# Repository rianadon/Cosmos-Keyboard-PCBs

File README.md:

# Cosmos Keyboard PCBs

This repository contains the sources and specs for the PCBs I've made for my pet project, [Cosmos Keyboard Generator](https://ryanis.cool/cosmos).

## Plum Twist

A single-key PCB, with hotswap and RGB support that locks into place. [[Main Website](https://ryanis.cool/cosmos/plum-twist/)] [[Buy](https://cosmos-store.ryanis.cool/products/plum-twist)]

It's similar in functionality to the [Amoeba PCBs](https://github.com/JKing-B16/keyboard-pcbs) (in fact I've used some of the same footprints), but I've switched to large SMD pads to make wiring easier and designed the footprint to twist into a custom socket.

The version here on GitHub is pared down in terms of artwork and panelization, as my goal here is to make it easy for you to produce your own functionally identical version, not copy 1:1 what I sell. It's cheaper through JLC to buy the non-panelized version anyways. See the [subfolder's README](./plum-twist/README.md) for instructions on manufacturing these yourself.

Pinouts and wiring instructions are [on the Plum Twist website](https://ryanis.cool/cosmos/plum-twist/wiring). *A choc version is sadly impossible because the choc hotswap socket is too large to enable twisting while keeping the PCB footprint small.*

## Lemon Microcontroller

An RP2040-based microcontroller with 2 spec-compliant USB ports, a VIK connector, and FPC connectors for connecting keys. [[Main Website](https://ryanis.cool/cosmos/lemon/)] [[Buy](https://cosmos-store.ryanis.cool/collections/lemon)]

The rightmost USB (closest to the RP2040 chip) is for programming. The leftmost PCB (by the SPI flash) cannot be used for programming. See the [subfolder's README](./lemon-wired/README.md) for pinouts, QMK examples, and more.

## Lemon Wireless Microcontroller

An NRF52840-based microcontroller with a USB port, battery connector & charger, on/off switch, a VIK connector, and FPC connectors for connecting keys. [[Main Website](https://ryanis.cool/cosmos/lemon/)] [[Buy](https://cosmos-store.ryanis.cool/collections/lemon)]

Because it uses a shift register to drive columns, this board is capable of driving large keyboards even with external modules and lighting. See the [subfolder's README](./lemon-wireless-uc/README.md) for more information.

## Cactus Connector

A splitter for VIK cables. [[Docs](https://ryanis.cool/cosmos/docs/pcbs/cactus-connector)] [[Buy](https://cosmos-store.ryanis.cool/products/cactus-connector-for-vik)]

## Licensing

I license the subprojects differently, so refer to each subdirectory for licensing information.

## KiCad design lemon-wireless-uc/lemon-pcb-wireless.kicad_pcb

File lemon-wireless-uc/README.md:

# Lemon Wireless Microcontroller

[Documentation is on the Cosmos Docs.](https://ryanis.cool/cosmos/docs/pcbs/lemon-wireless/)

## Pinouts

### V0.2 Pinout

[Click for pinout picture](./lemon-pcb-wireless-pinout-v02.png)

### V0.3 Pinout

[Click for pinout picture](./lemon-pcb-wireless-pinout-v03.png)

### V0.4 Pinout

## VIK Information

| Category                 | Classification          | Response           |
| -----------------------  | ----------------------- | ------------------ |
| FPC connector            | Required                | :heavy_check_mark: |
| Breakout pins            | Recommended             | :heavy_check_mark: |
| Supplies: SPI            | Required                | :heavy_check_mark: |
| Supplies: I2C            | Required                | :heavy_check_mark: |
| I2C on main PCB          | Discouraged             | no                 |
| I2C pull ups             | Informative             | N/A                |
| Supplies: RGB            | Required                | :heavy_check_mark: |
| Supplies: Extra GPIO 1   | Required                | Analog/Digital     |
| Supplies: Extra GPIO 2   | Required                | Analog/Digital     |

GPIO and SPI & I2C should be fully VIK-compatible. RGB can be used on one of the flex PCB connector, through-hole pad, or VIK module, but not multiple at the same time. This is a limitation of the flex PCB not having an RGB return pin. If you are using RGB through the VIK connector, solder the "RGB->VIK" jumper.

When connected to USB, 5V on the VIK connector will be 5V. However, it will be equal to battery voltage when operating off battery power (3.3-4.2V).

## License

Cosmos Keyboards invests time and resources providing this open source design, please support Cosmos and open-source hardware by purchasing products from Cosmos!

Designed by Ryan Adolf/rianadon for Cosmos Keyboards.

Creative Commons Attribution/Share-Alike, all text above must be included in any redistribution. See license.txt for additional details.

*adapted from Adafruit's Creative Commons Attribution/Share-Alike license.*

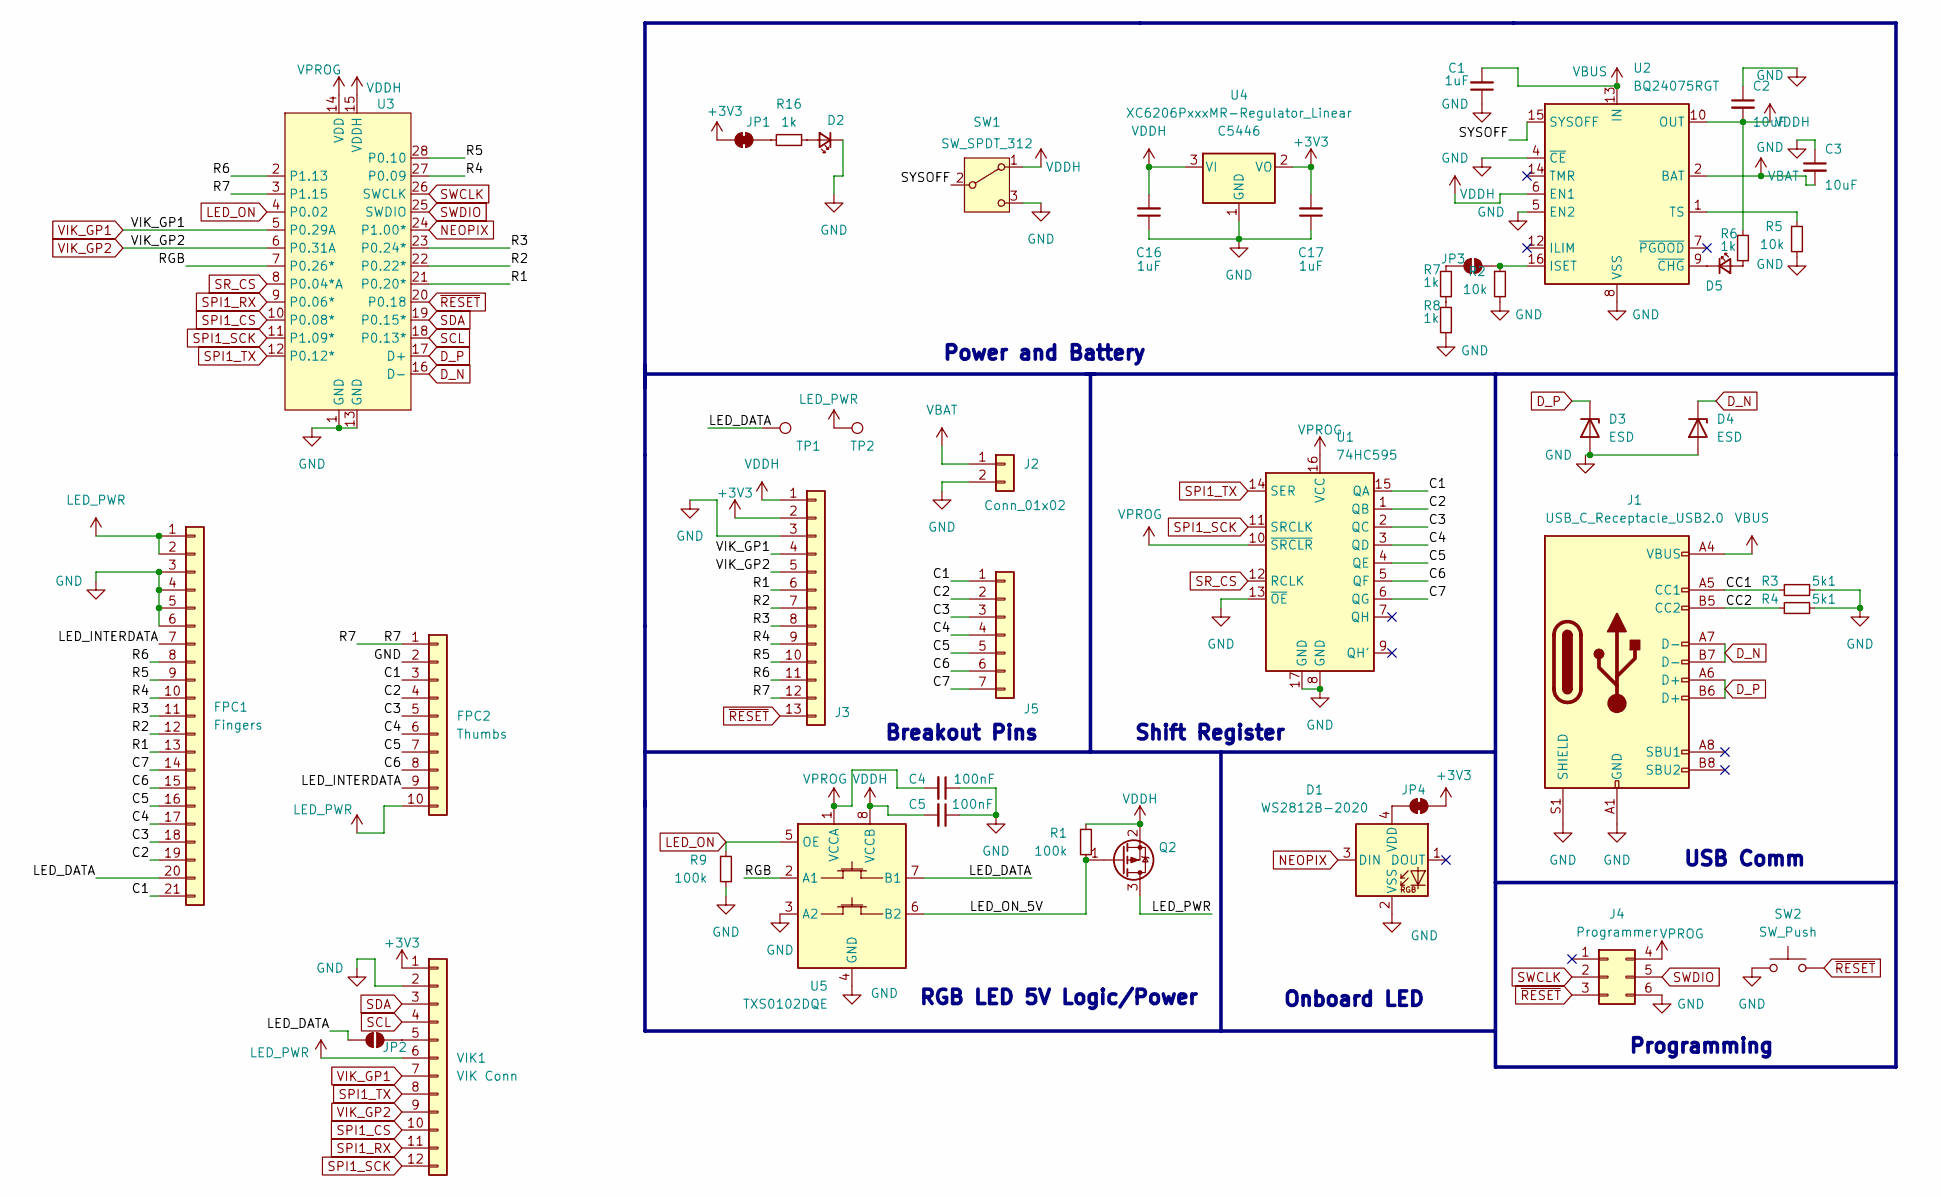
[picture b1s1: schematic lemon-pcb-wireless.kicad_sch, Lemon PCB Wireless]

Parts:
C1: 1uF; C_0402_1005Metric; LCSC C52923
C2, C3: 10uF; C_0402_1005Metric; LCSC C15525
C4, C5: 100nF; C_0402_1005Metric; LCSC C1525
C16, C17: 1uF; C_0603_1608Metric; LCSC C15849
D1: WS2812B-2020; LED_WS2812B-2020_PLCC4_2.0x2.0mm; LCSC C965555
D2: LED_Small; LED_0402_1005Metric; LCSC C7496802
D3, D4: ESD; D_SOD-523; LCSC C18723415
D5: LED_Small; LED_0402_1005Metric; LCSC C779448
FPC1: Fingers; FPC-SMD_21P-P0.30_HDGC_0.3K-QX-21PWB; LCSC C3012330
FPC2: Thumbs; FPC-SMD_10P-P0.50_HC-FPC-05-09-10RLTAG; LCSC C5213731
J1: USB_C_Receptacle_USB2.0; USB_C_Receptacle_HRO_TYPE-C-31-M-12; LCSC C165948
J2: Conn_01x02; JST_PH_S2B-PH-SM4-TB_1x02-1MP_P2.00mm_Horizontal; LCSC C295747
J3: Conn_01x11; PinHeader_1x13_P2.54mm_Vertical
J4: Programmer; j2thing
J5: Conn_01x11; PinHeader_1x07_P2.54mm_Vertical
JP1, JP4: SolderJumper_2_Bridged; SolderJumper-2_P1.3mm_Bridged_Pad1.0x1.5mm
JP2, JP3: SolderJumper_2_Open; SolderJumper-2_P1.3mm_Open_Pad1.0x1.5mm
Q2: Q_PMOS_SGD; SOT-23; LCSC C15127
R1, R9: 100k; R_0402_1005Metric; LCSC C25741
R2, R5: 10k; R_0402_1005Metric; LCSC C25744
R3, R4: 5k1; R_0402_1005Metric; LCSC C25905
R6, R7, R8, R16: 1k; R_0402_1005Metric; LCSC C11702
SW1: SW_SPDT_312; MK-12C02-G020_GSW; LCSC C963206
SW2: SW_Push; SW_Push_SPST_NO_Alps_SKRK; LCSC C115357
TP1, TP2: TestPoint; TestPoint_THTPad_D1.0mm_Drill0.5mm
U1: 74HC595; DHVQFN-16-1EP_2.5x3.5mm_P0.5mm_EP1x2mm; LCSC C730243
U2: BQ24075RGT; VQFN-16-1EP_3x3mm_P0.5mm_EP1.6x1.6mm; LCSC C15464
U3: XCVR_MS88SF2
U4: XC6206PxxxMR-Regulator_Linear; SOT-23; LCSC C5446
U5: TXS0102DQE; X2SON-8_1.4x1mm_P0.35mm
VIK1: VIK Conn; FPC-SMD_FPC05012-09200; LCSC C19273928

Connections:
+3V3: C17.2, J3.2, JP1.2 (B), JP4.2 (B), U4.2 (VO), VIK1.1
/C1: FPC1.21, FPC2.3, J5.1, U1.15 (QA)
/C2: FPC1.19, FPC2.4, J5.2, U1.1 (QB)
/C3: FPC1.18, FPC2.5, J5.3, U1.2 (QC)
/C4: FPC1.17, FPC2.6, J5.4, U1.3 (QD)
/C5: FPC1.16, FPC2.7, J5.5, U1.4 (QE)
/C6: FPC1.15, FPC2.8, J5.6, U1.5 (QF)
/C7: FPC1.14, J5.7, U1.6 (QG)
/CC1: J1.A5 (CC1), R3.1
/CC2: J1.B5 (CC2), R4.1
/LED_DATA: FPC1.20, JP2.1 (A), TP1.1, U5.7 (B1)
/LED_INTERDATA: FPC1.7, FPC2.9
/LED_ON_5V: Q2.1 (G), R1.2, U5.6 (B2)
/R1: FPC1.13, J3.6, U3.21 (P0.20*)
/R2: FPC1.12, J3.7, U3.22 (P0.22*)
/R3: FPC1.11, J3.8, U3.23 (P0.24*)
/R4: FPC1.10, J3.9, U3.27 (P0.09)
/R5: FPC1.9, J3.10, U3.28 (P0.10)
/R6: FPC1.8, J3.11, U3.2 (P1.13)
/R7: FPC2.1, J3.12, U3.3 (P1.15)
/RGB: U3.7 (P0.26*), U5.2 (A1)
/SYSOFF: SW1.2 (B), U2.15 (SYSOFF)
D_N: D4.1 (K), J1.A7 (D-), J1.B7 (D-), U3.16 (D-)
D_P: D3.1 (K), J1.A6 (D+), J1.B6 (D+), U3.17 (D+)
GND: C1.1, C2.1, C3.1, C4.1, C5.1, C16.1, C17.1, D1.2 (VSS), D2.1 (K), D3.2 (A), D4.2 (A), FPC1.3, FPC1.4, FPC1.5, FPC1.6, FPC2.2, J1.A1 (GND), J1.A12 (GND), J1.B1 (GND), J1.B12 (GND), J1.S1 (SHIELD), J2.2, J3.3, J4.6, R2.2, R3.2, R4.2, R5.2, R8.1, R9.2, SW1.3 (C), SW2.1, U1.8 (GND), U1.13 (~OE), U1.17 (GND), U2.4 (~CE), U2.5 (EN2), U2.8 (VSS), U2.17 (VSS), U3.1 (GND), U3.13 (GND), U4.1 (GND), U5.3 (A2), U5.4 (GND), VIK1.2
LED_ON: R9.1, U3.4 (P0.02), U5.5 (OE)
LED_PWR: FPC1.1, FPC1.2, FPC2.10, Q2.3 (D), TP2.1, VIK1.6
NEOPIX: D1.3 (DIN), U3.24 (P1.00*)
unnamed: D1.4 (VDD), JP4.1 (A)
unnamed: D2.2 (A), R16.2
unnamed: D5.2 (A), R6.1
unnamed: D5.1 (K), U2.9 (~CHG)
unnamed: JP1.1 (A), R16.1
unnamed: JP2.2 (B), VIK1.5
unnamed: JP3.1 (A), R2.1, U2.16 (ISET)
unnamed: JP3.2 (B), R7.2
unnamed: R7.1, R8.2
unnamed: R5.1, U2.1 (TS)
SCL: U3.18 (P0.13*), VIK1.4
SDA: U3.19 (P0.15*), VIK1.3
SPI1_CS: U3.10 (P0.08*), VIK1.10
SPI1_RX: U3.9 (P0.06*), VIK1.11
SPI1_SCK: U1.11 (SRCLK), U3.11 (P1.09*), VIK1.12
SPI1_TX: U1.14 (SER), U3.12 (P0.12*), VIK1.8
SR_CS: U1.12 (RCLK), U3.8 (P0.04*A)
SWCLK: J4.2, U3.26 (SWCLK)
SWDIO: J4.5, U3.25 (SWDIO)
VBAT: C3.2, J2.1, U2.2 (BAT), U2.3 (BAT)
VBUS: C1.2, J1.A4 (VBUS), J1.A9 (VBUS), J1.B4 (VBUS), J1.B9 (VBUS), U2.13 (IN)
VDDH: C2.2, C5.2, C16.2, J3.1, Q2.2 (S), R1.1, R6.2, SW1.1 (A), U2.6 (EN1), U2.10 (OUT), U2.11 (OUT), U3.15 (VDDH), U4.3 (VI), U5.8 (VCCB)
VIK_GP1: J3.4, U3.5 (P0.29A), VIK1.7
VIK_GP2: J3.5, U3.6 (P0.31A), VIK1.9
VPROG: C4.2, J4.4, U1.10 (~SRCLR), U1.16 (VCC), U3.14 (VDD), U5.1 (VCCA)
~RESET: J3.13, J4.3, SW2.2, U3.20 (P0.18)

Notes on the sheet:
RGB LED 5V Logic/Power
Breakout Pins
Programming
Shift Register
USB Comm
Power and Battery
Onboard LED

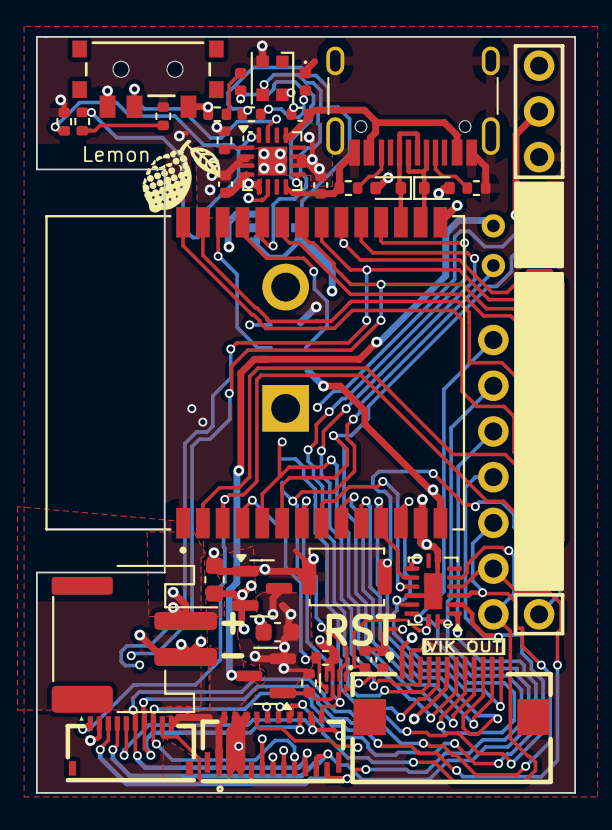
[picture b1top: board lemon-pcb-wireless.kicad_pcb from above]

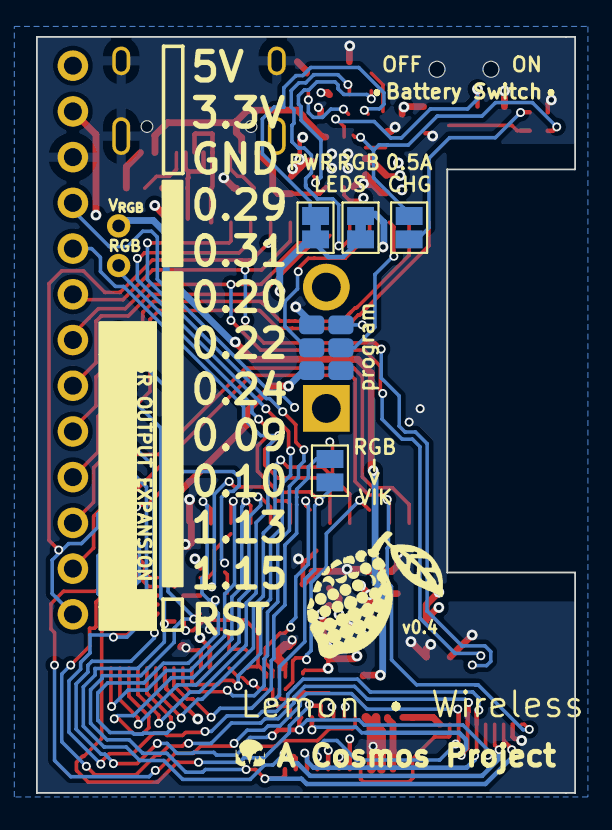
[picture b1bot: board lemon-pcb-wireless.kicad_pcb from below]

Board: 4 copper layers, 29.9 x 42.0 mm, 44 parts (7 on the bottom side), 54 nets.

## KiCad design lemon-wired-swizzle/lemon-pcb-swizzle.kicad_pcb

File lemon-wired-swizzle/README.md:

# Lemon Wired Swizzle Microcontroller

This is a version of the Lemon Wired that swap the two USB ports depending on which one has power incoming.

The pinout is equivalent to v0.4 of the Lemon Wired. However, while GP16 was previously now unused, it's now the software override for the USB swap.

## Theory of operation

I use LM6620 to isolate the the VBUS voltages on both USB sockets. This part has an ST pin that indicates which VBUS was powered. This ST pin drives sel, and if sel is not overwrittten by GP16, then the two USB data lines are swapped using FSUSB42MUX.

Shortly after the device is powered on, power is applied to both VBUS using a PMOS with an RC circuit at the gate to ensure there is a delay so that ST can settle before both VBUS are turned on. Because of the hysteresis on LM6620, turning on both VBUS does not change the ST pin.

## License

Cosmos Keyboards invests time and resources providing this open source design, please support Cosmos and open-source hardware by purchasing products from Cosmos!

Designed by Ryan Adolf/rianadon for Cosmos Keyboards.

Creative Commons Attribution/Share-Alike, all text above must be included in any redistribution. See license.txt for additional details.

*adapted from Adafruit's Creative Commons Attribution/Share-Alike license.*

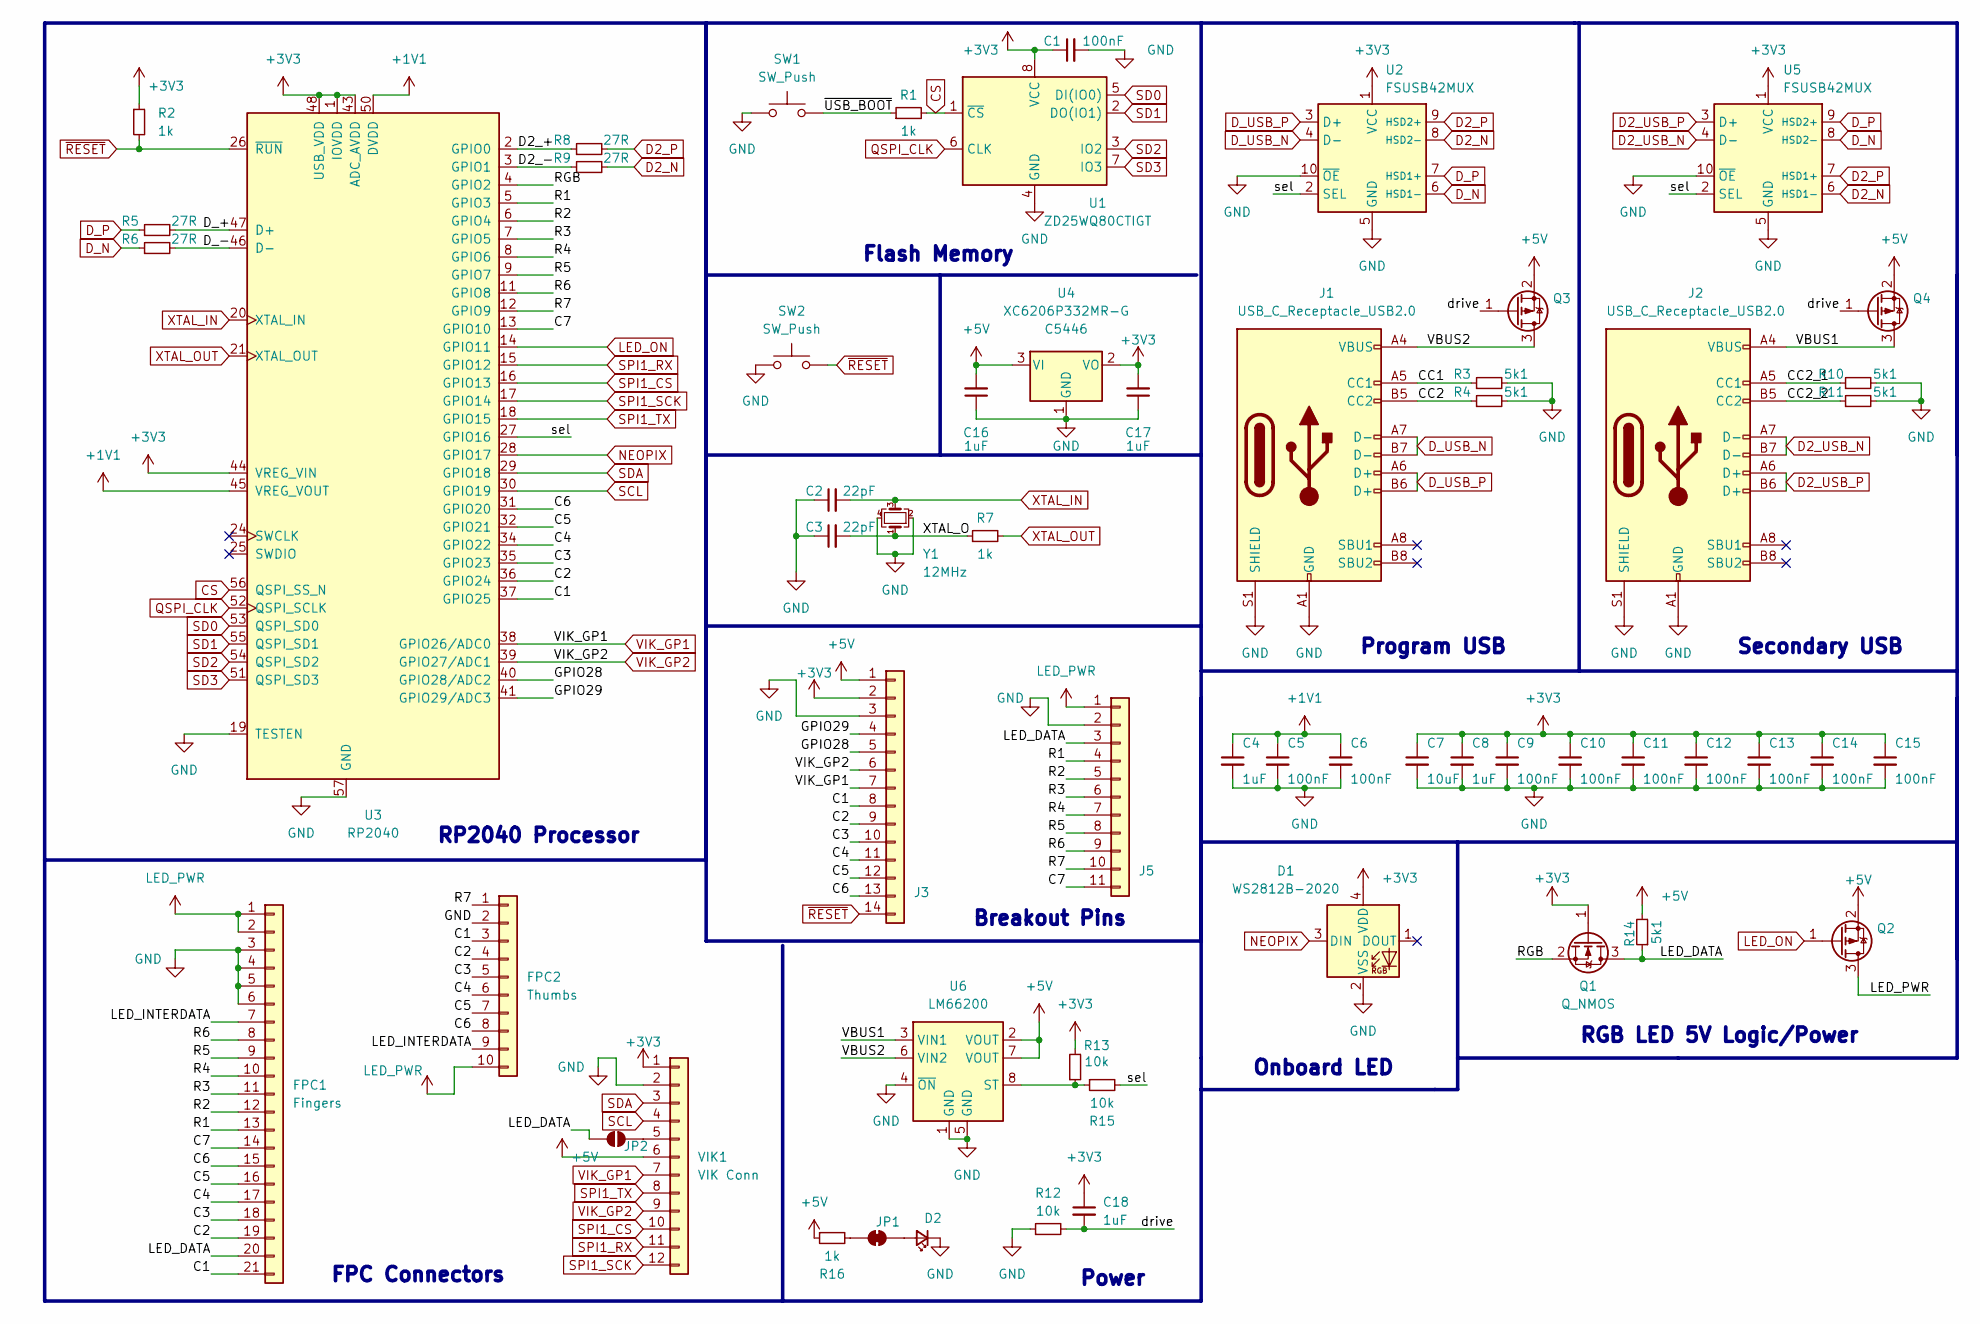
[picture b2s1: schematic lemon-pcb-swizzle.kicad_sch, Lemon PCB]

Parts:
C1, C5, C6, C9, C10, C11, C12, C13, C14, C15: 100nF; C_0402_1005Metric; LCSC C1525
C2, C3: 22pF; C_0402_1005Metric; LCSC C1555
C4, C8, C18: 1uF; C_0402_1005Metric; LCSC C52923
C7: 10uF; C_0402_1005Metric; LCSC C15525
C16, C17: 1uF; C_0603_1608Metric; LCSC C15849
D1: WS2812B-2020; LED_WS2812B-2020_PLCC4_2.0x2.0mm; LCSC C965555
D2: LED_Small; LED_0603_1608Metric; LCSC C7371898
FPC1: Fingers; LCSC C2919509
FPC2: Thumbs; LCSC C5213731
J1, J2: USB_C_Receptacle_USB2.0; USB_C_Receptacle_HRO_TYPE-C-31-M-12; LCSC C165948
J3: Conn_01x11; PinHeader_1x14_P2.54mm_Vertical
J5: Conn_01x11; PinHeader_1x11_P2.54mm_Vertical
JP1: SolderJumper_2_Bridged; SolderJumper-2_P1.3mm_Bridged_Pad1.0x1.5mm
JP2: SolderJumper_2_Open; SolderJumper-2_P1.3mm_Open_Pad1.0x1.5mm
Q1: Q_NMOS; SOT-23; LCSC C8545
Q2, Q3, Q4: Q_PMOS_SGD; SOT-23; LCSC C15127
R1, R2, R7, R16: 1k; R_0402_1005Metric; LCSC C11702
R3, R4, R10, R11, R14: 5k1; R_0402_1005Metric; LCSC C25905
R5, R6, R8, R9: 27R; R_0603_1608Metric; LCSC C25190
R12, R13, R15: 10k; R_0402_1005Metric; LCSC C25744
SW1, SW2: SW_Push; SW_Push_SPST_NO_Alps_SKRK; LCSC C115357
U1: ZD25WQ80CTIGT; SOP-8_3.9x4.9mm_P1.27mm; LCSC C7525143
U2, U5: FSUSB42MUX; MSOP-10_3x3mm_P0.5mm; LCSC C11355
U3: RP2040; RP2040-QFN-56; LCSC C2040
U4: XC6206P332MR-G; SOT-23; LCSC C5446
U6: LM66200; SOT-583-8; LCSC C3235556
VIK1: VIK Conn; LCSC C479750
Y1: 12MHz; Crystal_SMD_3225-4Pin_3.2x2.5mm; LCSC C9002

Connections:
+1V1: C4.1, C5.1, C6.1, U3.23 (DVDD), U3.45 (VREG_VOUT), U3.50 (DVDD)
+3V3: C1.1, C7.1, C8.1, C9.1, C10.1, C11.1, C12.1, C13.1, C14.1, C15.1, C17.2, C18.1, D1.4 (VDD), J3.2, Q1.1 (G), R2.1, R13.2, U1.8 (VCC), U2.1 (VCC), U3.1 (IOVDD), U3.10 (IOVDD), U3.22 (IOVDD), U3.33 (IOVDD), U3.42 (IOVDD), U3.43 (ADC_AVDD), U3.44 (VREG_VIN), U3.48 (USB_VDD), U3.49 (IOVDD), U4.2 (VO), U5.1 (VCC), VIK1.1
+5V: C16.2, J3.1, Q2.2 (S), Q3.2 (S), Q4.2 (S), R14.2, R16.1, U4.3 (VI), U6.2 (VOUT), U6.7 (VOUT), VIK1.6
/C1: FPC1.21, FPC2.3, J3.8, U3.37 (GPIO25)
/C2: FPC1.19, FPC2.4, J3.9, U3.36 (GPIO24)
/C3: FPC1.18, FPC2.5, J3.10, U3.35 (GPIO23)
/C4: FPC1.17, FPC2.6, J3.11, U3.34 (GPIO22)
/C5: FPC1.16, FPC2.7, J3.12, U3.32 (GPIO21)
/C6: FPC1.15, FPC2.8, J3.13, U3.31 (GPIO20)
/C7: FPC1.14, J5.11, U3.13 (GPIO10)
/CC1: J1.A5 (CC1), R3.1
/CC2: J1.B5 (CC2), R4.1
/CC2_1: J2.A5 (CC1), R10.1
/CC2_2: J2.B5 (CC2), R11.1
/D2_+: R8.1, U3.2 (GPIO0)
/D2_-: R9.1, U3.3 (GPIO1)
/D_+: R5.2, U3.47 (D+)
/D_-: R6.2, U3.46 (D-)
/GPIO28: J3.5, U3.40 (GPIO28/ADC2)
/GPIO29: J3.4, U3.41 (GPIO29/ADC3)
/LED_DATA: FPC1.20, J5.3, JP2.1 (A), Q1.3 (D), R14.1
/LED_INTERDATA: FPC1.7, FPC2.9
/R1: FPC1.13, J5.4, U3.5 (GPIO3)
/R2: FPC1.12, J5.5, U3.6 (GPIO4)
/R3: FPC1.11, J5.6, U3.7 (GPIO5)
/R4: FPC1.10, J5.7, U3.8 (GPIO6)
/R5: FPC1.9, J5.8, U3.9 (GPIO7)
/R6: FPC1.8, J5.9, U3.11 (GPIO8)
/R7: FPC2.1, J5.10, U3.12 (GPIO9)
/RGB: Q1.2 (S), U3.4 (GPIO2)
/VBUS1: J2.A4 (VBUS), J2.A9 (VBUS), J2.B4 (VBUS), J2.B9 (VBUS), Q4.3 (D), U6.3 (VIN1)
/VBUS2: J1.A4 (VBUS), J1.A9 (VBUS), J1.B4 (VBUS), J1.B9 (VBUS), Q3.3 (D), U6.6 (VIN2)
/XTAL_O: C3.2, R7.1, Y1.1
/drive: C18.2, Q3.1 (G), Q4.1 (G), R12.2
/sel: R15.2, U2.2 (SEL), U3.27 (GPIO16), U5.2 (SEL)
/~USB_BOOT: R1.1, SW1.2
CS: R1.2, U1.1 (~CS), U3.56 (QSPI_SS_N)
D2_N: R9.2, U2.8 (HSD2-), U5.6 (HSD1-)
D2_P: R8.2, U2.9 (HSD2+), U5.7 (HSD1+)
D2_USB_N: J2.A7 (D-), J2.B7 (D-), U5.4 (D-)
D2_USB_P: J2.A6 (D+), J2.B6 (D+), U5.3 (D+)
D_N: R6.1, U2.6 (HSD1-), U5.8 (HSD2-)
D_P: R5.1, U2.7 (HSD1+), U5.9 (HSD2+)
D_USB_N: J1.A7 (D-), J1.B7 (D-), U2.4 (D-)
D_USB_P: J1.A6 (D+), J1.B6 (D+), U2.3 (D+)
GND: C1.2, C2.1, C3.1, C4.2, C5.2, C6.2, C7.2, C8.2, C9.2, C10.2, C11.2, C12.2, C13.2, C14.2, C15.2, C16.1, C17.1, D1.2 (VSS), D2.1 (K), FPC1.3, FPC1.4, FPC1.5, FPC1.6, FPC2.2, J1.A1 (GND), J1.A12 (GND), J1.B1 (GND), J1.B12 (GND), J1.S1 (SHIELD), J2.A1 (GND), J2.A12 (GND), J2.B1 (GND), J2.B12 (GND), J2.S1 (SHIELD), J3.3, J5.2, R3.2, R4.2, R10.2, R11.2, R12.1, SW1.1, SW2.1, U1.4 (GND), U2.5 (GND), U2.10 (~OE), U3.19 (TESTEN), U3.57 (GND), U4.1 (GND), U5.5 (GND), U5.10 (~OE), U6.1 (GND), U6.4 (~ON), U6.5 (GND), VIK1.2, Y1.2, Y1.4
LED_ON: Q2.1 (G), U3.14 (GPIO11)
LED_PWR: FPC1.1, FPC1.2, FPC2.10, J5.1, Q2.3 (D)
NEOPIX: D1.3 (DIN), U3.28 (GPIO17)
unnamed: D2.2 (A), JP1.2 (B)
unnamed: JP1.1 (A), R16.2
unnamed: JP2.2 (B), VIK1.5
unnamed: R13.1, R15.1, U6.8 (ST)
QSPI_CLK: U1.6 (CLK), U3.52 (QSPI_SCLK)
SCL: U3.30 (GPIO19), VIK1.4
SD0: U1.5 (DI(IO0)), U3.53 (QSPI_SD0)
SD1: U1.2 (DO(IO1)), U3.55 (QSPI_SD1)
SD2: U1.3 (IO2), U3.54 (QSPI_SD2)
SD3: U1.7 (IO3), U3.51 (QSPI_SD3)
SDA: U3.29 (GPIO18), VIK1.3
SPI1_CS: U3.16 (GPIO13), VIK1.10
SPI1_RX: U3.15 (GPIO12), VIK1.11
SPI1_SCK: U3.17 (GPIO14), VIK1.12
SPI1_TX: U3.18 (GPIO15), VIK1.8
VIK_GP1: J3.7, U3.38 (GPIO26/ADC0), VIK1.7
VIK_GP2: J3.6, U3.39 (GPIO27/ADC1), VIK1.9
XTAL_IN: C2.2, U3.20 (XTAL_IN), Y1.3
XTAL_OUT: R7.2, U3.21 (XTAL_OUT)
~RESET: J3.14, R2.2, SW2.2, U3.26 (~RUN)

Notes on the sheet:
FPC Connectors
Program USB
RP2040 Processor
Secondary USB
Breakout Pins
Onboard LED
Power
Flash Memory
RGB LED 5V Logic/Power

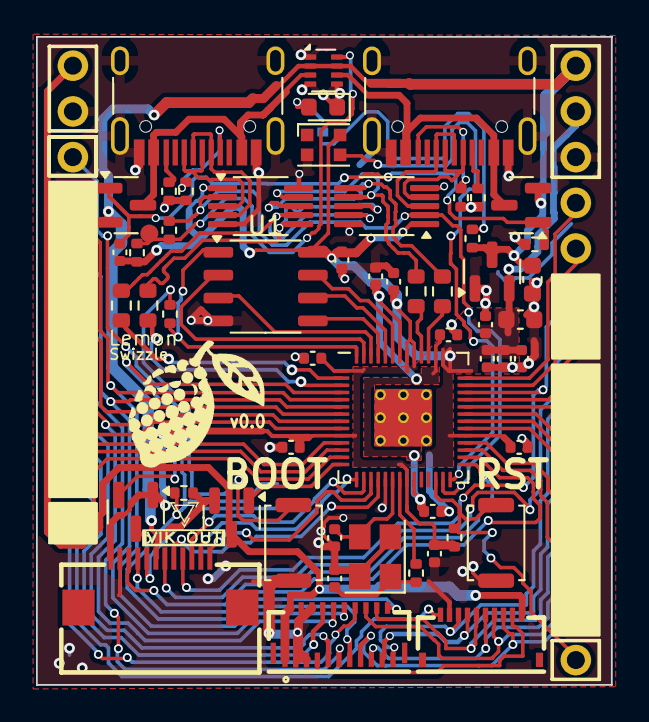
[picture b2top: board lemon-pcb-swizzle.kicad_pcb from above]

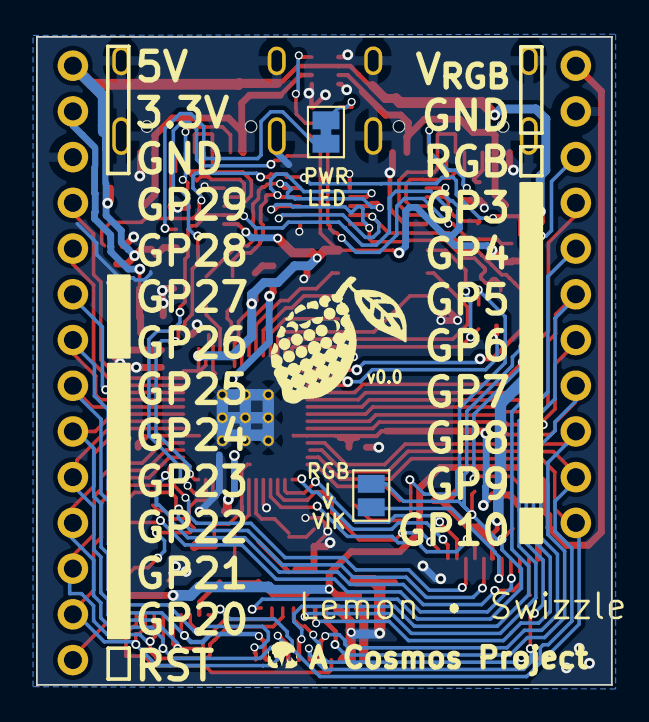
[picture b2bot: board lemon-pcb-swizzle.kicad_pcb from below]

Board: 2 copper layers, 31.9 x 36.0 mm, 59 parts (4 on the bottom side), 69 nets.

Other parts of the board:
svg2mod: G***; vik_small

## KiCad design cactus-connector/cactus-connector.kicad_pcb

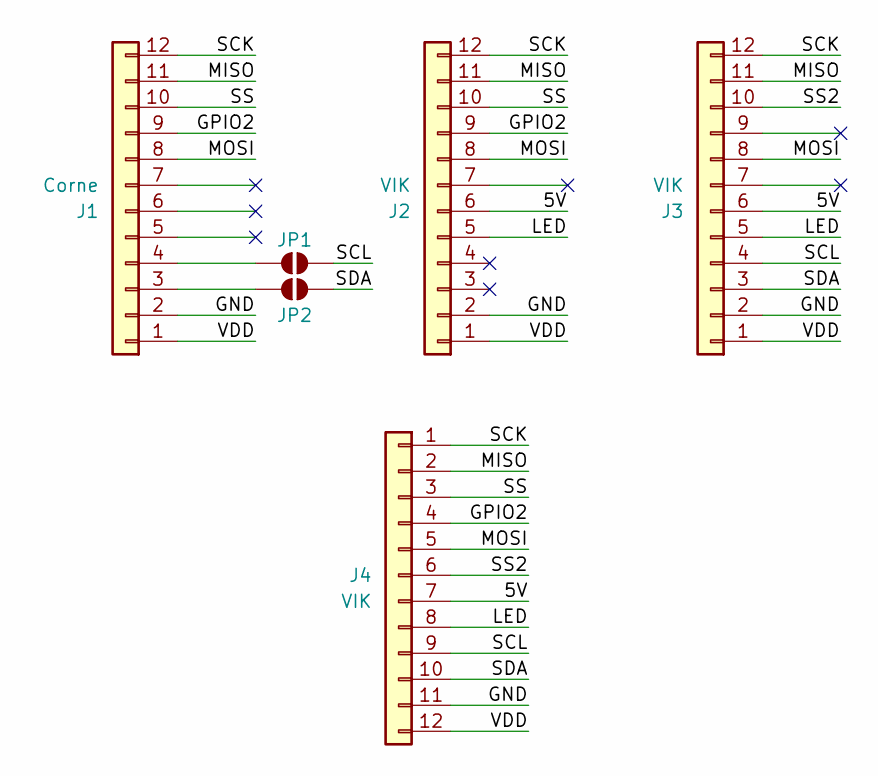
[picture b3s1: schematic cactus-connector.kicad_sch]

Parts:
J1: Corne; fpc
J2, J3, J4: VIK; fpc
JP1, JP2: SolderJumper_2_Open; SolderJumper-2_P1.3mm_Open_RoundedPad1.0x1.5mm

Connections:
/5V: J2.6, J3.6, J4.7
/GND: J1.2, J2.2, J3.2, J4.11
/GPIO2: J1.9, J2.9, J4.4
/LED: J2.5, J3.5, J4.8
/MISO: J1.11, J2.11, J3.11, J4.2
/MOSI: J1.8, J2.8, J3.8, J4.5
/SCK: J1.12, J2.12, J3.12, J4.1
/SCL: J3.4, J4.9, JP1.2 (B)
/SDA: J3.3, J4.10, JP2.2 (B)
/SS: J1.10, J2.10, J4.3
/SS2: J3.10, J4.6
/VDD: J1.1, J2.1, J3.1, J4.12
unnamed: J1.3, JP2.1 (A)
unnamed: J1.4, JP1.1 (A)

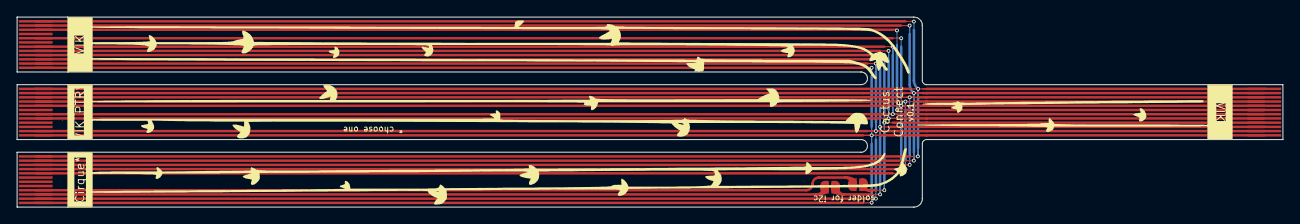
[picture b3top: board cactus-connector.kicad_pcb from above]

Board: 2 copper layers, 149.9 x 22.5 mm, 6 parts (0 on the bottom side), 14 nets.

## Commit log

2024-12-07 README and Lemon QMK example
2024-12-08 Add gerbers for Plum Twist
2025-01-29 Add lemon_test sketch
2025-02-12 Add lemon 0.2 files
2025-02-20 Add microcontrollers, restructure README
2025-02-20 Add wireless schematic pdf
2025-02-20 Images
2025-03-24 Update Wired Lemon V03 information
2025-03-27 Add pretty pictures
2025-03-27 Update pinout diagram
2025-03-27 Update wireless pinout
2025-06-24 Bring Plum Twist in repo up to date with store version
2025-07-14 Update gerbers & remove extra silkscreen
2025-07-25 Lemon wired V0.4, Lemon wireless V0.3
2025-07-25 Add VIK information
2025-09-25 [Plum Twist] Add assembly instructions
    Fixes #1
2025-10-28 Add LED test UF2
2025-11-30 Add Cactus Connector
2026-03-13 Rename lemon-microcontroller folder
2026-03-13 Lemon wired swizzle
2026-04-27 Lemon Wireless v0.4
